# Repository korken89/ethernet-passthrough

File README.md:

# Ethernet Pass-through Test

## TODO

* Give Ethernet IC its own clock
* Add PoE with pass-through?
* Route board

## Good links to keep

* https://ww1.microchip.com/downloads/en/DeviceDoc/00002335B.pdf
* http://ww1.microchip.com/downloads/en/DeviceDoc/KSZ8863RLL-Hardware-Design-Checklist-00003048B.pdf
* https://github.com/adamgreig/linetime/blob/master/hardware/r1_notes.md
* https://github.com/AirborneEngineering/blethrs
* https://github.com/smoltcp-rs/smoltcp
* https://github.com/stm32-rs/stm32-eth
* https://github.com/mitchmindtree/mdio

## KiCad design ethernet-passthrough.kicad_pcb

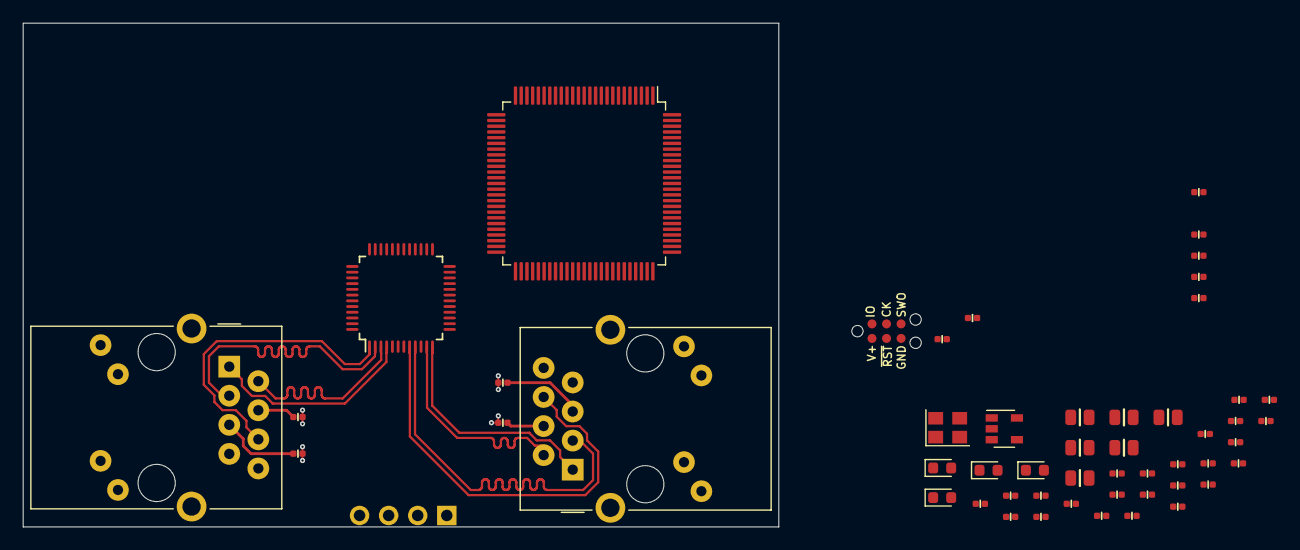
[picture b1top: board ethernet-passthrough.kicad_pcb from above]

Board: 4 copper layers, 66.0 x 44.0 mm, 53 parts (0 on the bottom side), 56 nets.

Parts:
C1, C4, C5, C6, C7, C8, C9, C10, C11, C14, C17, C18, C19, C22, C23, C24, C25, C26: 0.1u; C_0402
C2, C3: 2.2u; C_0402
C12, C13, C15, C16, C20, C21: 22u; C_0805
D1, D2, D3, D4: GREEN; LED_0603_1608Metric
FB1, FB2: Ferrite_Bead_Small; R_0402
J1: tag-connect-swd; tag-connect_6pin_nolegs_swd
J2: Conn_01x04_Male; 1x4_2.54mm
J3, J4: RJ45_Amphenol_RJMG1BD3B8K1ANR
R1, R2, R3, R4, R10, R11, R12, R13: 1k; R_0402
R5, R8: 10k; R_0402
R6, R7: 4.7k; R_0402
R9: 11.8k; R_0402
U1: STM32F407VETx; LQFP-100_14x14mm_P0.5mm
U2: KSZ8863RLL; LQFP-48_7x7mm_Pitch0.5mm
U3: MIC5219-3.3YM5; SOT-23-5
X1: 25 MHz; Oscillator_SMD_Abracon_ASE-4Pin_3.2x2.5mm

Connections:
+3V3: C1.1, C5.1, C6.1, C7.1, C8.1, C9.1, C10.1, C11.1, C14.1, C16.1, C18.1, C20.1, FB1.2, J1.1, R6.1, R7.1, U1.6, U1.11, U1.19, U1.21, U1.22, U1.28, U1.50, U1.75, U1.100, U2.22, U2.40, U3.5, X1.1, X1.4
+5V: C12.1, J2.1, U3.1, U3.3
/1.8V: C21.1, C22.1, FB2.2, U2.32, U2.42
/ETH_CRS_DV: U1.32, U2.25
/ETH_MDC: U1.16, U2.36
/ETH_MDIO: R6.2, U1.25, U2.37
/ETH_REFCLK: U1.24, U2.23, U2.26
/ETH_RST: R8.1, U1.47, U2.47
/ETH_RXD0: U1.33, U2.29
/ETH_RXD1: U1.34, U2.28
/ETH_TXD0: U1.51, U2.20
/ETH_TXD1: U1.52, U2.19
/ETH_TX_EN: U1.48, U2.16
/ISET: R9.2, U2.6
/LINK1: R11.1, U2.44
/LINK2: R13.1, U2.46
/MCO: U1.67, U2.14
/NRST: C4.2, J1.3, U1.14
/RX1_N: J3.R6, U2.1
/RX1_P: J3.R3, U2.2
/RX2_N: J4.R6, U2.8
/RX2_P: J4.R3, U2.9
/SWCLK: J1.4, U1.76
/SWDIO: J1.2, U1.72
/TRAFFIC1: R10.1, U2.43
/TRAFFIC2: R12.1, U2.45
/TX1_N: J3.R2, U2.3
/TX1_P: J3.R1, U2.4
/TX2_N: J4.R2, U2.11
/TX2_P: J4.R1, U2.12
/USART1_RX: J2.2, U1.69
/USART1_TX: J2.3, U1.68
/VDDA_1V8: C15.1, C19.1, FB2.1, U2.7
/VDDA_3V3: C13.1, C17.1, FB1.1, U2.5
GND: C1.2, C2.1, C3.1, C4.1, C5.2, C6.2, C7.2, C8.2, C9.2, C10.2, C11.2, C12.2, C13.2, C14.2, C15.2, C16.2, C17.2, C18.2, C19.2, C20.2, C21.2, C22.2, C23.2, C24.2, C25.2, C26.2, D1.1, D2.1, D3.1, D4.1, J1.5, J2.4, J3.13, J3.L2, J3.L3, J3.R8, J4.13, J4.L2, J4.L3, J4.R8, R5.2, R8.2, R9.1, U1.10, U1.20, U1.27, U1.74, U1.99, U2.10, U2.21, U2.31, U2.41, U3.2, X1.2
unnamed: C2.2, U1.49
unnamed: C3.2, U1.73
unnamed: C23.1, J3.R4
unnamed: C24.1, J3.R5
unnamed: C25.1, J4.R4
unnamed: C26.1, J4.R5
unnamed: D1.2, R1.2
unnamed: D2.2, R2.2
unnamed: D3.2, R3.2
unnamed: D4.2, R4.2
unnamed: J3.L1, R11.2
unnamed: J3.L4, R10.2
unnamed: J4.L1, R13.2
unnamed: J4.L4, R12.2
unnamed: R1.1, U1.1
unnamed: R2.1, U1.2
unnamed: R3.1, U1.3
unnamed: R4.1, U1.4
unnamed: R5.1, U1.94
unnamed: R7.2, U2.39
unnamed: U1.12, X1.3

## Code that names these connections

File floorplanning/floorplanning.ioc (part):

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PH0-OSC_IN.Signal=RCC_OSC_IN
PA7.Mode=RMII
PA10.Mode=Asynchronous
Mcu.UserName=STM32F407VETx
PC4.Signal=ETH_RXD0
PC5.Mode=RMII
PB11.Signal=ETH_TX_EN
PB13.Signal=ETH_TXD1
PA13.Signal=SYS_JTMS-SWDIO
PA9.Mode=Asynchronous
PB11.Mode=RMII
PA9.Signal=USART1_TX
PA1.Signal=ETH_REF_CLK
PH0-OSC_IN.Mode=HSE-External-Clock-Source
RCC.HSE_VALUE=25000000
board=custom
PA1.Mode=RMII
PA14.Mode=Serial_Wire
PH1-OSC_OUT.Signal=RCC_OSC_OUT
PA8.Signal=RCC_MCO_1
PA13.Mode=Serial_Wire
Mcu.Name=STM32F407V(E-G)Tx
PA2.Signal=ETH_MDIO
PH1-OSC_OUT.Mode=HSE-External-Clock-Source
RCC.SYSCLKFreq_VALUE=16000000
Mcu.Package=LQFP100
PB12.Mode=RMII
PA10.Signal=USART1_RX
PA14.Signal=SYS_JTCK-SWCLK
PA2.Mode=RMII
PA8.Mode=Clock-out-1
PC5.Signal=ETH_RXD1
PB13.Mode=RMII
PC1.Signal=ETH_MDC
PB12.Signal=ETH_TXD0
PC4.Mode=RMII
PC1.Mode=RMII
PA7.Signal=ETH_CRS_DV

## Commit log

2021-01-11 cap on 5V
2021-01-12 more work
